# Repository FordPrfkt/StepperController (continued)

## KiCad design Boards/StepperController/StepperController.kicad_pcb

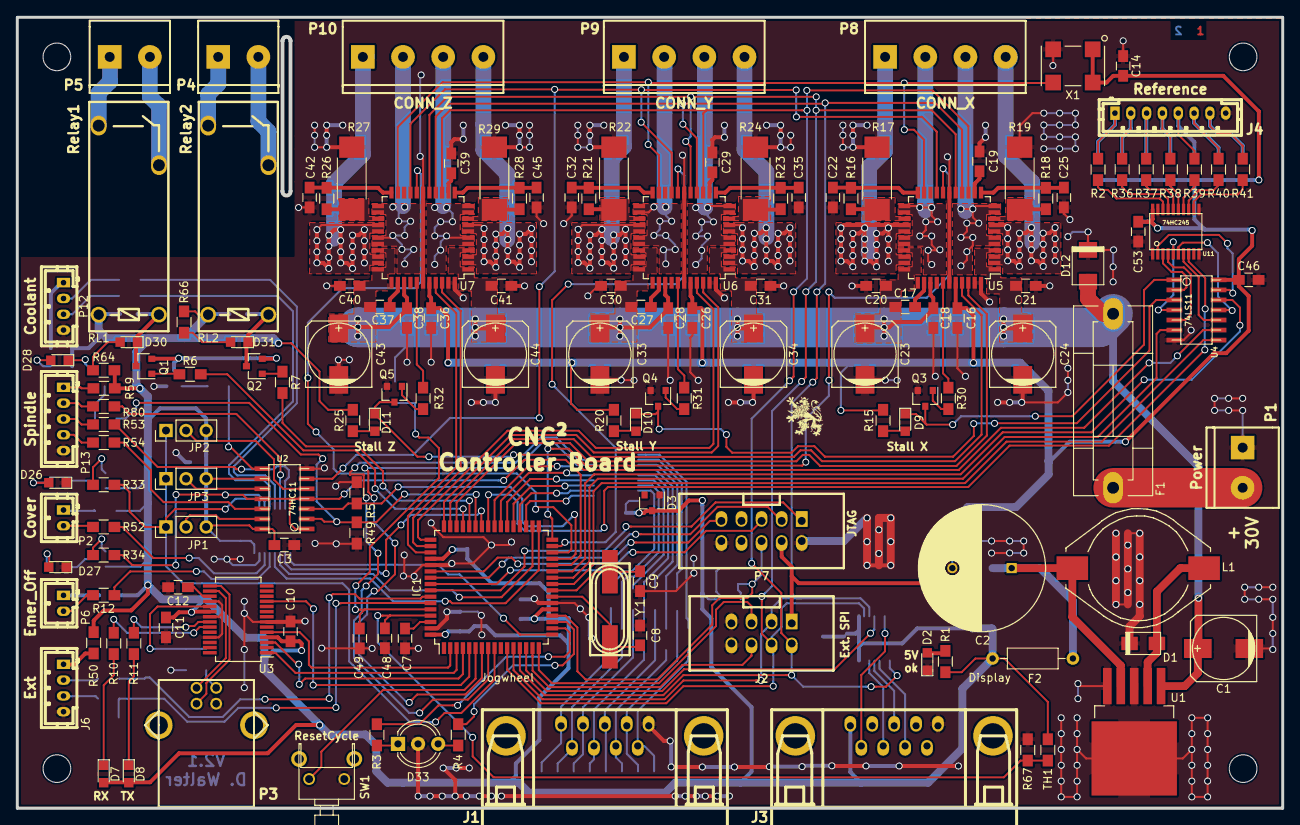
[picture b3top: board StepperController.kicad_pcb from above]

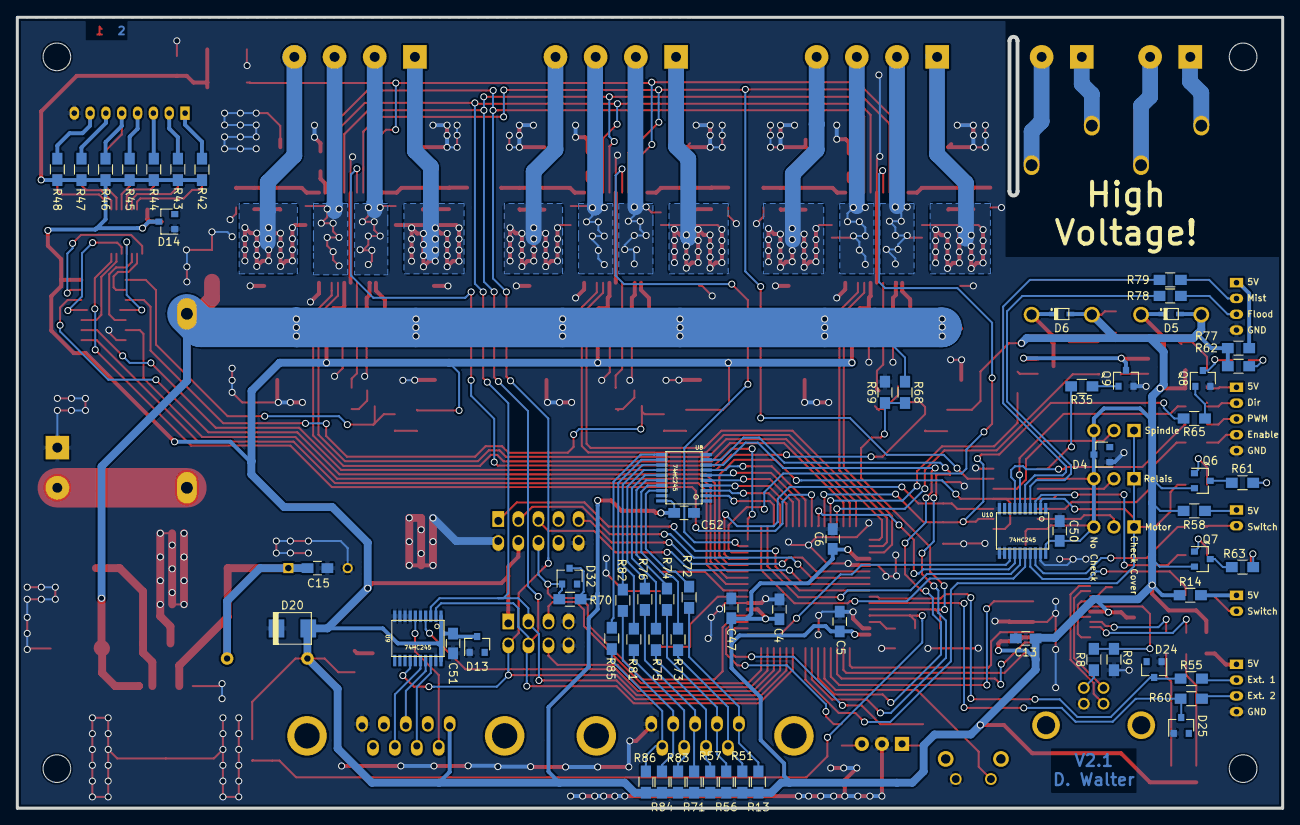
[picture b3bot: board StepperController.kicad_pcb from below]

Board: 2 copper layers, 160.0 x 100.0 mm, 213 parts (65 on the bottom side), 204 nets.

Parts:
C1, C23, C24, C33, C34, C43, C44: 100µF; c_elec_8x10.5
C2: 1000µF; C_Radial_D16_L25_P7.5
C3, C4, C5, C6, C7, C10, C12, C14, C16, C17, C18, C20, C21, C26, C27, C28, C30, C31, C36, C37, C38, C40, C41, C46, C48, C49, C50, C51, C52, C53: 100nF; C_0805_HandSoldering
C8, C9: 22pF; C_0805_HandSoldering
C11: 100nf; C_0805_HandSoldering
C13: 4,7µF; C_0805_HandSoldering
C15, C47: 10µF; C_0805_HandSoldering
C19, C29, C32, C39: 470nF; C_0805_HandSoldering
C22, C25, C35, C42, C45: 10nF; C_0805_HandSoldering
D1: SK34; do214ac
D2: LED_GN; LED_0805
D3, D4, D13, D14, D24, D25: ZMY5,6; D_SOT-23_ANK
D5, D6: 1N4148; sod323
D7, D8: LED_YE; LED_0805
D9, D10, D11: LED_RT; LED_0805
D12: SM6T 30CA; do214aa
D20: P6SMB 6,8A; do214aa
D26, D27: LED_Rd; LED_0805
D28, D30, D31: LED_Gn; LED_0805
D32: ZMY5.6; D_SOT-23_ANK
D33: Led_x2; LED_D5.0mm-3
F1: 10AT; Fuseholder5x20_horiz_SemiClosed_Casing10x25mm
F2: 4AT; R_Axial_DIN0207_L6.3mm_D2.5mm_P10.16mm_Horizontal
IC1: ATMEGA128-A; TQFP-64_14x14mm_Pitch0.8mm
J1, J3: DB9_Female; DB_9F
J2: SPI_Extern; vasch_strip_4x2
J4: Reference; b8b-ph-kl
J6: Ext; b4b-ph-kl
JP1, JP2, JP3: JUMPER3; Pin_Header_Straight_1x03_Pitch2.54mm
L1: L-PISR 100µH; Choke_SMD_PISR_Handsoldering_FASTRON
P1: Power; mors_2p
P2: Cover; b2b-ph-kl
P3: USB_B; conn_usb_B
P4: Relay2; mors_2p
P5: Relay1; mors_2p
P6: Emer_Off; b2b-ph-kl
P7: JTAG; vasch_strip_5x2
P8: CONN_X; mors_4p
P9: CONN_Y; mors_4p
P10: CONN_Z; mors_4p
P12: Coolant; b4b-ph-kl
P13: Spindle; b5b-ph-kl
Q1, Q2, Q3, Q4, Q5, Q8, Q9: BC817-40; SOT-23
Q6, Q7: BC807-40; SOT-23
R1, R3, R62, R64, R66: 140R; R_0805_HandSoldering
R2, R12, R14, R36, R37, R38, R39, R40, R41, R52, R53, R54, R55, R58, R60, R72, R73, R74, R75, R76, R78, R79, R80, R81, R82, R85: 100R; R_0805_HandSoldering
R4, R15, R20, R25, R61, R63: 160R; R_0805_HandSoldering
R5, R9, R49: 10k; R_0805_HandSoldering
R6, R7, R33, R34, R35: 1k; R_0805_HandSoldering
R8, R13, R30, R31, R32, R42, R43, R44, R45, R46, R47, R48, R51, R56, R57, R65, R71, R83, R84, R86: 4k7; R_0805_HandSoldering
R10, R11: 150R; R_0805_HandSoldering
R16, R18, R23, R26, R28: 22R; R_0805_HandSoldering
R17, R19, R24, R27, R29: 100mR; R_2512_HandSoldering
R21, R50, R59, R77: 10R; R_0805_HandSoldering
R22: 150mR; R_2512_HandSoldering
R67: 3k6; R_0805_HandSoldering
R68: 8k6; R_0805_HandSoldering
R69: 1k2; R_0805_HandSoldering
R70: 12k; R_0805_HandSoldering
RL1, RL2: FINDER-36.11-4301; Fujiutsu_JS-MT
SW1: ResetCycle; SW_0773
TH1: 6k8; R_0805_HandSoldering
U1: LM2576S-5; TO-263-5Lead
U2: 74HC11; so-14
U3: FT232RL; SSOP-28_5.3x10.2mm_Pitch0.65mm
U4: 74LS11; so-14
U5, U6, U7: TMC2660; TQFP-44_10x10mm_Pitch0.8mm
U8, U9, U10, U11: 74HC245; tssop-20
X1: 16MHz; XO91
Y1: 16MHz; hc-49_smd

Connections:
+5V: C3.1, C4.1, C5.1, C6.1, C10.1, C11.1, C13.1, C14.1, C16.1, C26.1, C36.1, C46.1, C47.1, C50.1, C51.1, C52.1, C53.1, D3.1, D4.1, D5.1, D6.1, D7.2, D8.2, D13.1, D14.1, D20.1, D32.1, F2.2, IC1.21, IC1.52, IC1.64, J2.1, J3.5, JP1.3, JP2.3, JP3.3, P7.4, Q6.2, Q7.2, R1.1, R13.1, R14.1, R15.1, R20.1, R25.2, R42.1, R43.1, R44.1, R45.1, R46.1, R47.1, R48.1, R50.1, R51.1, R56.1, R57.1, R58.1, R59.1, R62.1, R64.1, R66.1, R70.1, R71.1, R77.1, R83.1, R84.1, R86.1, RL1.A1, RL2.A1, TH1.1, U2.9, U2.14, U3.4, U3.20, U4.14, U5.40, U6.40, U7.40, U8.20, U9.1, U9.20, U10.20, U11.20, X1.1, X1.4
/Controller/CS_Ext1: IC1.15, J2.6
/Controller/CS_Ext2: IC1.16, J2.5
/Controller/CS_X: IC1.32, U5.18
/Controller/CS_Y: IC1.31, U6.18
/Controller/CS_Z: IC1.30, U7.18
/Controller/CTS: IC1.5, U3.11
/Controller/Cool_Flood: IC1.33, U10.16
/Controller/Cool_Mist: IC1.34, U10.15
/Controller/Cover: IC1.9, JP1.1, JP2.1, JP3.1, R33.2, U10.2
/Controller/CycleStart: IC1.8, U8.9
/Controller/Dir_X: IC1.47, U5.41
/Controller/Dir_Y: IC1.49, U6.41
/Controller/Dir_Z: IC1.51, U7.41
/Controller/Emergency_Off: IC1.28, R34.2, U2.1, U2.4, U2.11, U10.3
/Controller/Enable: IC1.29, R5.1, U2.3
/Controller/Ext1: D24.1, IC1.58, R55.1
/Controller/Ext2: D25.1, IC1.59, R60.1
/Controller/FeedHold: IC1.7, U8.8
/Controller/JogA: IC1.35, U8.2
/Controller/JogB: IC1.36, U8.3
/Controller/JogC: IC1.37, U8.4
/Controller/JogX: IC1.38, U8.5
/Controller/JogY: IC1.39, U8.6
/Controller/JogZ: IC1.40, U8.7
/Controller/LED1: IC1.18, R3.2
/Controller/LED2: IC1.19, R4.2
/Controller/RTS: IC1.4, U3.3
/Controller/RXD: IC1.2, U3.5
/Controller/Ref_X1: U4.13, U11.2
/Controller/Ref_X2: U4.2, U11.3
/Controller/Ref_Y1: U4.5, U11.4
/Controller/Ref_Y2: U4.4, U11.5
/Controller/Ref_Z1: U4.11, U11.6
/Controller/Ref_Z2: U4.10, U11.7
/Controller/Rel_1: IC1.45, R6.2
/Controller/Rel_2: IC1.44, R7.2
/Controller/Reset: D32.2, IC1.20, P7.6, R70.2
/Controller/SCK: IC1.11, J2.4, U5.16, U6.16, U7.16, U9.2
/Controller/SDI: IC1.12, J2.3, U5.15, U6.15, U7.15, U9.3
/Controller/SDO: IC1.13, J2.2, U5.14, U6.14, U7.14, U9.14
/Controller/Spindle_Dir: IC1.42, U10.14
/Controller/Spindle_PWM: IC1.17, U10.13
/Controller/Stall_X: D9.1, Q3.3, U4.1
/Controller/Stall_Y: D10.1, Q4.3, U4.3
/Controller/Stall_Z: D11.1, Q5.3, U4.9
/Controller/Step_X: IC1.46, U5.42
/Controller/Step_Y: IC1.48, U6.42
/Controller/Step_Z: IC1.50, U7.42
/Controller/TXD: IC1.3, U3.1
/Controller/T_REG: C48.1, IC1.61, R67.1, TH1.2
/Controller/V_SUP: C49.1, IC1.60, R68.2, R69.1
/Driver/Driver_X/BRA_X: R18.1, R19.2, U5.9
/Driver/Driver_X/BRB_X: R16.1, R17.2, U5.25
/Driver/Driver_X/OA1_X: P8.4, U5.2, U5.3, U5.7, U5.8
/Driver/Driver_X/OA2_X: P8.3, U5.5, U5.6, U5.10, U5.11
/Driver/Driver_X/OB1_X: P8.1, U5.26, U5.27, U5.31, U5.32
/Driver/Driver_X/OB2_X: P8.2, U5.23, U5.24, U5.28, U5.29
/Driver/Driver_X/SRA_X: C25.2, R18.2, U5.12
/Driver/Driver_X/SRB_X: C22.2, R16.2, U5.22
/Driver/Driver_Y/BRA_Y: R23.1, R24.2, U6.9
/Driver/Driver_Y/BRB_Y: R21.1, R22.2, U6.25
/Driver/Driver_Y/OA1_Y: P9.4, U6.2, U6.3, U6.7, U6.8
/Driver/Driver_Y/OA2_Y: P9.3, U6.5, U6.6, U6.10, U6.11
/Driver/Driver_Y/OB1_Y: P9.1, U6.26, U6.27, U6.31, U6.32
/Driver/Driver_Y/OB2_Y: P9.2, U6.23, U6.24, U6.28, U6.29
/Driver/Driver_Y/SRA_Y: C35.2, R23.2, U6.12
/Driver/Driver_Y/SRB_Y: C32.2, R21.2, U6.22
/Driver/Driver_Z/BRA_Z: R28.1, R29.2, U7.9
/Driver/Driver_Z/BRB_Z: R26.1, R27.2, U7.25
/Driver/Driver_Z/OA1_Z: P10.4, U7.2, U7.3, U7.7, U7.8
/Driver/Driver_Z/OA2_Z: P10.3, U7.5, U7.6, U7.10, U7.11
/Driver/Driver_Z/OB1_Z: P10.1, U7.26, U7.27, U7.31, U7.32
/Driver/Driver_Z/OB2_Z: P10.2, U7.23, U7.24, U7.28, U7.29
/Driver/Driver_Z/SRA_Z: C45.2, R28.2, U7.12
/Driver/Driver_Z/SRB_Z: C42.2, R26.2, U7.22
/Driver/TMC_Clock: U5.21, U6.21, U7.21, X1.3
/Driver/TMC_Enable: U2.6, U5.19, U6.19, U7.19
/Interface/CS_Disp: IC1.14, U9.4
/Interface/D+: P3.3, U3.15
/Interface/D-: P3.2, U3.16
/Interface/LED_RX: R11.2, U3.22
/Interface/LED_TX: R10.2, U3.23
/Interface/Ref_T1: IC1.41, U11.8
/Interface/Reset_UART: R8.2, R9.1, U3.19
/Interface/Spindle_Enable: IC1.43, R49.2, R65.2, U2.2
/Interface/VCC_USB: P3.1, R8.1
GND: C1.2, C2.2, C3.2, C4.2, C5.2, C6.2, C7.2, C8.2, C9.2, C10.2, C11.2, C12.2, C13.2, C14.2, C15.2, C16.2, C18.2, C19.2, C20.2, C21.2, C22.1, C23.2, C24.2, C25.1, C26.2, C28.2, C29.2, C30.2, C31.2, C32.1, C33.2, C34.2, C35.1, C36.2, C38.2, C39.2, C40.2, C41.2, C42.1, C43.2, C44.2, C45.1, C46.2, C47.2, C48.2, C49.2, C50.2, C51.2, C52.2, C53.2, D1.2, D2.1, D3.2, D4.2, D12.2, D13.2, D14.2, D20.2, D24.2, D25.2, D26.1, D27.1, D33.2, IC1.22, IC1.53, IC1.63, J1.1, J2.7, J2.8, J3.1, J4.8, J6.4, P1.1, P3.4, P7.2, P7.10, P12.4, P13.5, Q3.2, Q4.2, Q5.2, Q8.2, Q9.2, R5.2, R9.2, R17.1, R19.1, R22.1, R24.1, R27.1, R29.1, R49.1, R67.2, R69.2, SW1.2, U1.3, U1.5, U2.7, U3.7, U3.18, U3.21, U3.25, U4.7, U5.17, U5.39, U5.43, U5.44, U6.17, U6.39, U6.43, U6.44, U7.17, U7.39, U7.43, U7.44, U8.1, U8.10, U8.19, U9.5, U9.7, U9.8, U9.9, U9.10, U9.19, U10.1, U10.10, U10.11, U10.12, U10.19, U11.1, U11.10, U11.11, U11.19, X1.2
unnamed: C7.1, IC1.62
unnamed: C8.1, IC1.23, Y1.2
unnamed: C9.1, IC1.24, Y1.1
unnamed: C12.1, U3.17
unnamed: C2.1, C15.1, F2.1, L1.2, U1.4
unnamed: C17.2, U5.35
unnamed: C19.1, U5.13
unnamed: C27.2, U6.35
unnamed: C29.1, U6.13
unnamed: C37.2, U7.35
unnamed: C39.1, U7.13
unnamed: D1.1, L1.1, U1.2
unnamed: D2.2, R1.2
unnamed: D7.1, R10.1
unnamed: D8.1, R11.1
unnamed: D9.2, R15.2
unnamed: D10.2, R20.2
unnamed: D11.2, R25.1
unnamed: D26.2, R61.1
unnamed: D27.2, R63.2
unnamed: D28.1, Q8.3
unnamed: D28.2, R62.2
unnamed: D5.2, D30.1, Q1.3, RL1.A2
unnamed: D30.2, R64.2
unnamed: D6.2, D31.1, Q2.3, RL2.A2
unnamed: D31.2, R66.2
unnamed: D33.1, R3.1
unnamed: D33.3, R4.1
unnamed: F1.1, P1.2
unnamed: IC1.6, SW1.1
unnamed: IC1.25, U4.8
unnamed: IC1.26, U4.6
unnamed: IC1.27, U4.12
unnamed: IC1.54, P7.9
unnamed: IC1.55, P7.3
unnamed: IC1.56, P7.5
unnamed: IC1.57, P7.1
unnamed: J1.2, R82.2, R84.2
unnamed: J1.3, R71.2, R76.2
unnamed: J1.4, R56.2, R74.2
unnamed: J1.5, R13.2, R72.2
unnamed: J1.6, R85.2, R86.2
unnamed: J1.7, R81.2, R83.2
unnamed: J1.8, R57.2, R75.2
unnamed: J1.9, R51.2, R73.2
unnamed: J3.3, U9.17
unnamed: J3.7, U9.16
unnamed: J3.8, U9.18
unnamed: J3.9, U9.6
unnamed: J4.1, R2.2, R42.2
unnamed: J4.2, R36.2, R43.2
unnamed: J4.3, R37.2, R44.2
unnamed: J4.4, R38.2, R45.2
unnamed: J4.5, R39.2, R46.2
unnamed: J4.6, R40.2, R47.2
unnamed: J4.7, R41.2, R48.2
unnamed: J6.1, R50.2
unnamed: J6.2, R55.2
unnamed: J6.3, R60.2
unnamed: JP1.2, U2.13
unnamed: JP2.2, U2.5
unnamed: JP3.2, U2.10
unnamed: P2.1, R58.2
unnamed: P2.2, R52.2
unnamed: P4.1, RL2.14
unnamed: P4.2, RL2.11
unnamed: P5.1, RL1.14
unnamed: P5.2, RL1.11
unnamed: P6.1, R14.2
unnamed: P6.2, R12.2
unnamed: P12.1, R77.2
unnamed: P12.2, R79.2
unnamed: P12.3, R78.2
unnamed: P13.1, R59.2
unnamed: P13.2, R80.2
unnamed: P13.3, R53.2
unnamed: P13.4, R54.2
unnamed: Q1.1, R6.1
unnamed: Q1.2, Q2.2, Q9.3
unnamed: Q2.1, R7.1
unnamed: Q3.1, R30.2
unnamed: Q4.1, R31.2
unnamed: Q5.1, R32.1
unnamed: Q6.1, R33.1
unnamed: Q6.3, R61.2
unnamed: Q7.1, R34.1
unnamed: Q7.3, R63.1
unnamed: Q8.1, R65.1
unnamed: Q9.1, R35.1
unnamed: R2.1, U11.18
unnamed: R12.1, U10.17
unnamed: R30.1, U5.38
unnamed: R31.1, U6.38
unnamed: R32.2, U7.38
unnamed: R35.2, U2.8
unnamed: R36.1, U11.17
unnamed: R37.1, U11.16
unnamed: R38.1, U11.15
unnamed: R39.1, U11.14
unnamed: R40.1, U11.13
unnamed: R41.1, U11.12
unnamed: R52.1, U10.18
unnamed: R53.1, U10.7
unnamed: R54.1, U2.12
unnamed: R72.1, U8.18
unnamed: R73.1, U8.17
unnamed: R74.1, U8.16
unnamed: R75.1, U8.15
unnamed: R76.1, U8.14
unnamed: R78.1, U10.4
unnamed: R79.1, U10.5
unnamed: R80.1, U10.6
unnamed: R81.1, U8.13
unnamed: R82.1, U8.12
unnamed: R85.1, U8.11
VSA: C1.1, C17.1, C18.1, C20.1, C21.1, C23.1, C24.1, C27.1, C28.1, C30.1, C31.1, C33.1, C34.1, C37.1, C38.1, C40.1, C41.1, C43.1, C44.1, D12.1, F1.2, R68.1, U1.1, U5.1, U5.4, U5.30, U5.33, U5.36, U6.1, U6.4, U6.30, U6.33, U6.36, U7.1, U7.4, U7.30, U7.33, U7.36

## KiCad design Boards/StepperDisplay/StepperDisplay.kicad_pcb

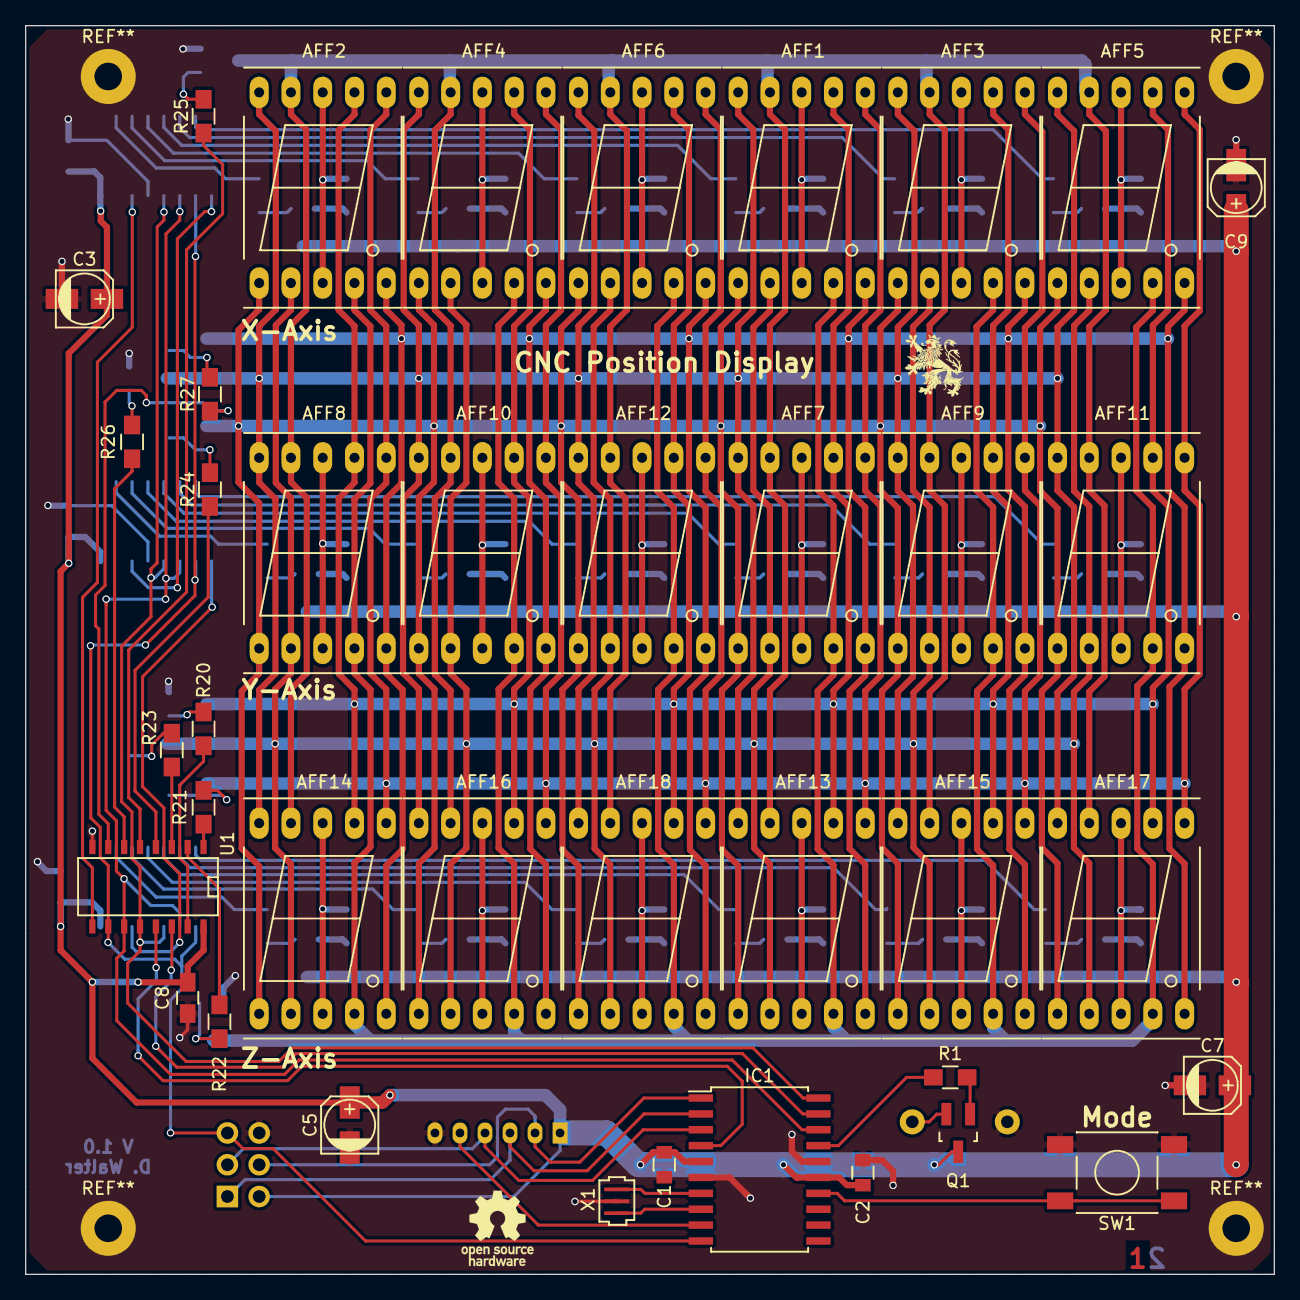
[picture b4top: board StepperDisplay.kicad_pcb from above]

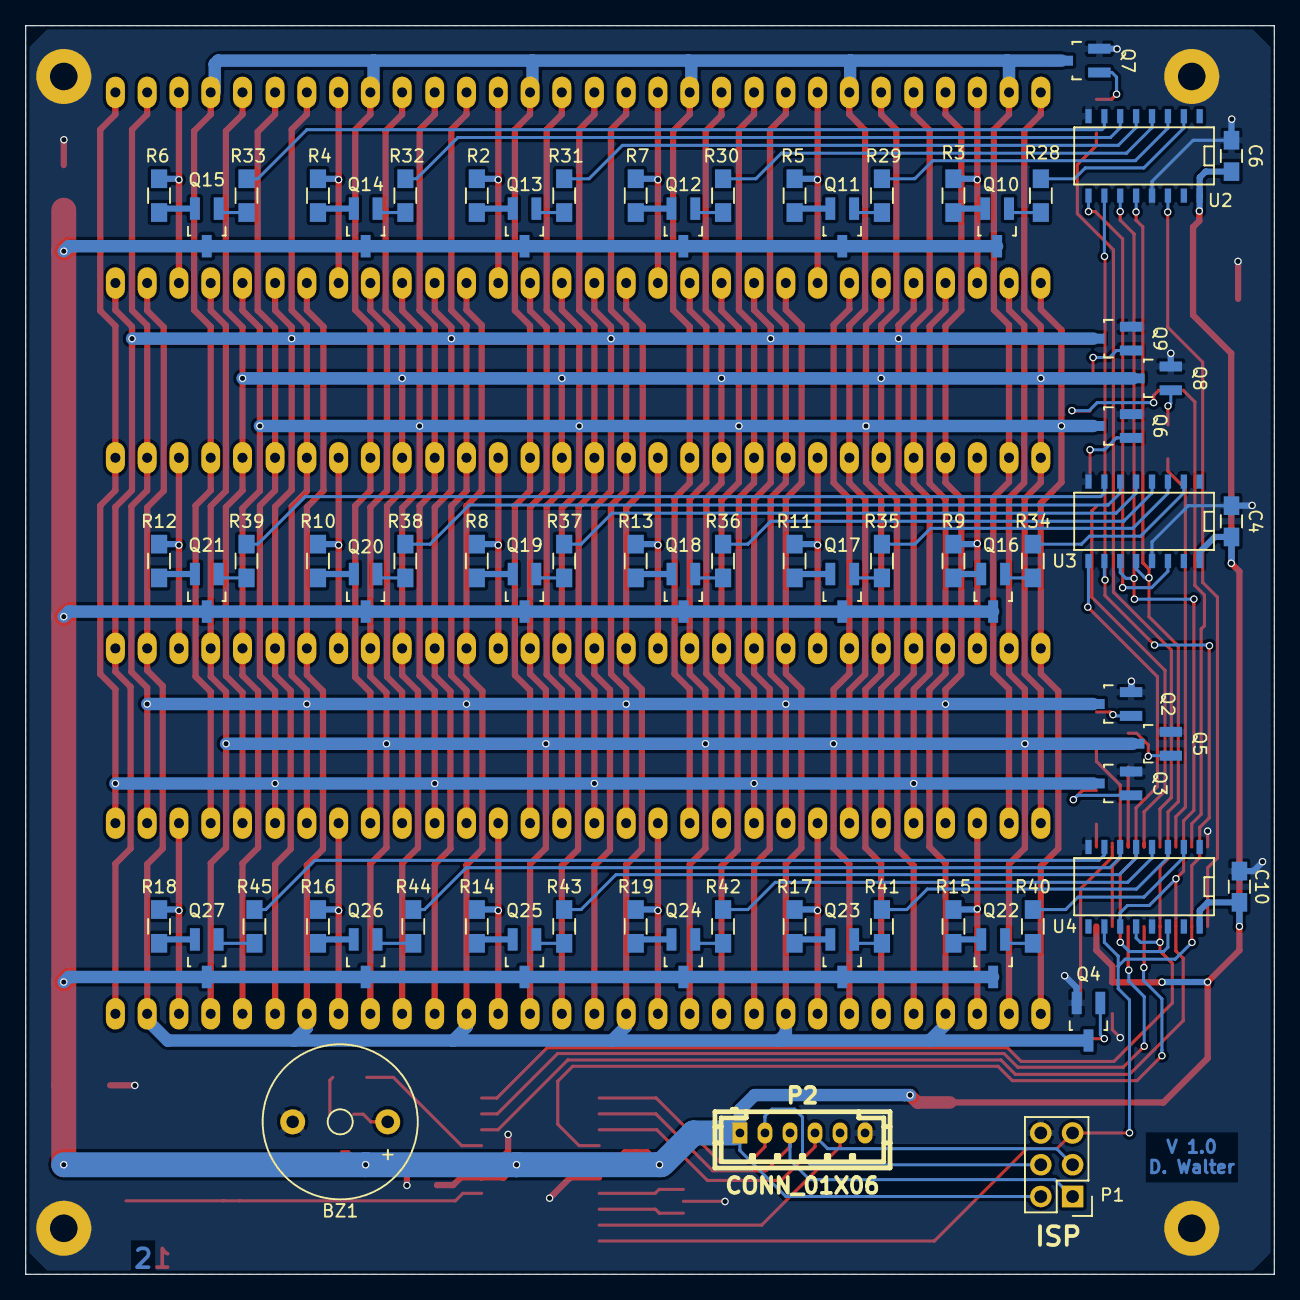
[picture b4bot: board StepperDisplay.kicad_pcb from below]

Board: 2 copper layers, 99.8 x 99.8 mm, 110 parts (71 on the bottom side), 116 nets.

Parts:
AFF1, AFF2, AFF3, AFF4, AFF5, AFF6, AFF7, AFF8, AFF9, AFF10, AFF11, AFF12, AFF13, AFF14, AFF15, AFF16, AFF17, AFF18: 7SEGMENTS; 7SegmentLED_LTS6760_LTS6780
BZ1: buzzer; Buzzer_12x9.5RM7.6
C1, C2: 100nF; C_0805
C3, C5, C7, C9: 100µF; c_elec_4x5.8
C4, C6, C8, C10: 100nF; C_0805_HandSoldering
IC1: ATTINY861-P; SOIC-20_7.5x12.8mm_Pitch1.27mm
P1: ISP; Pin_Header_Straight_2x03
P2: CONN_01X06; b6b-ph-kl
Q1, Q10, Q11, Q12, Q13, Q14, Q15, Q16, Q17, Q18, Q19, Q20, Q21, Q22, Q23, Q24, Q25, Q26, Q27: BC817-40; SOT-23_Handsoldering
Q2, Q3, Q4, Q5, Q6, Q7, Q8, Q9: IRLML2502; SOT-23_Handsoldering
R1, R28, R29, R30, R31, R32, R33, R34, R35, R36, R37, R38, R39, R40, R41, R42, R43, R44, R45: 1k; R_0805_HandSoldering
R2, R3, R4, R5, R6, R7, R8, R9, R10, R11, R12, R13, R14, R15, R16, R17, R18, R19: 18R; R_0805_HandSoldering
R20, R21, R22, R23, R24, R25, R26, R27: 100R; R_0805_HandSoldering
SW1: SW_PUSH; SW_LSx_1301
U1, U2, U3, U4: 74HC595; SO-16-N
X1: 12MHz; Resonator_CSTCE

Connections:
+5V: C1.1, C2.1, C3.1, C4.1, C5.1, C6.1, C7.1, C8.1, C9.1, C10.1, IC1.5, IC1.15, P1.2, P2.1, Q1.3, Q10.3, Q11.3, Q12.3, Q13.3, Q14.3, Q15.3, Q16.3, Q17.3, Q18.3, Q19.3, Q20.3, Q21.3, Q22.3, Q23.3, Q24.3, Q25.3, Q26.3, Q27.3, U1.16, U2.16, U3.16, U4.16
/Controller/Enable: IC1.4, U1.13
/Controller/R_Clock: IC1.20, U1.12, U2.12, U3.12, U4.12
/Controller/Reset: IC1.10, P1.5, U1.10, U2.10, U3.10, U4.10
/Controller/Ser_Clock: IC1.18, U1.11, U2.11, U3.11, U4.11
/LEDS/LEDsX/Ser_In: U1.9, U2.14
/LEDS/LEDsY/Ser_In: U2.9, U3.14
/LEDS/LEDsZ/Ser_In: U3.9, U4.14
/LEDS/Q1: R20.2, U1.15
/LEDS/Q2: R21.2, U1.1
/LEDS/Q3: R22.2, U1.2
/LEDS/Q4: R23.2, U1.3
/LEDS/Q5: R24.2, U1.4
/LEDS/Q6: R25.2, U1.5
/LEDS/Q7: R26.2, U1.6
/LEDS/Q8: R27.2, U1.7
/LEDS/Ser_In: IC1.19, U1.14
GND: BZ1.2, C1.2, C2.2, C3.2, C4.2, C5.2, C6.2, C7.2, C8.2, C9.2, C10.2, IC1.6, IC1.16, P1.6, P2.6, Q2.2, Q3.2, Q4.2, Q5.2, Q6.2, Q7.2, Q8.2, Q9.2, SW1.2, U1.8, U2.8, U2.13, U3.8, U3.13, U4.8, U4.13, X1.2
unnamed: AFF1.3, AFF1.8, R2.2
unnamed: AFF2.3, AFF2.8, R3.2
unnamed: AFF3.3, AFF3.8, R4.2
unnamed: AFF4.3, AFF4.8, R5.2
unnamed: AFF5.3, AFF5.8, R6.2
unnamed: AFF6.3, AFF6.8, R7.2
unnamed: AFF7.3, AFF7.8, R8.2
unnamed: AFF8.3, AFF8.8, R9.2
unnamed: AFF9.3, AFF9.8, R10.2
unnamed: AFF10.3, AFF10.8, R11.2
unnamed: AFF11.3, AFF11.8, R12.2
unnamed: AFF12.3, AFF12.8, R13.2
unnamed: AFF13.3, AFF13.8, R14.2
unnamed: AFF14.3, AFF14.8, R15.2
unnamed: AFF15.3, AFF15.8, R16.2
unnamed: AFF16.3, AFF16.8, R17.2
unnamed: AFF17.3, AFF17.8, R18.2
unnamed: AFF18.3, AFF18.8, R19.2
unnamed: BZ1.1, Q1.2
unnamed: IC1.1, P1.4, P2.2
unnamed: IC1.2, P1.1, P2.3
unnamed: IC1.3, P1.3, P2.4
unnamed: IC1.7, X1.3
unnamed: IC1.8, X1.1
unnamed: IC1.9, P2.5
unnamed: IC1.14, SW1.1
unnamed: IC1.17, R1.2
unnamed: Q1.1, R1.1
unnamed: Q2.1, R20.1
unnamed: Q3.1, R21.1
unnamed: Q4.1, R22.1
unnamed: Q5.1, R23.1
unnamed: Q6.1, R24.1
unnamed: Q7.1, R25.1
unnamed: Q8.1, R26.1
unnamed: Q9.1, R27.1
unnamed: Q10.1, R28.1
unnamed: Q10.2, R3.1
unnamed: Q11.1, R29.1
unnamed: Q11.2, R5.1
unnamed: Q12.1, R30.1
unnamed: Q12.2, R7.1
unnamed: Q13.1, R31.1
unnamed: Q13.2, R2.1
unnamed: Q14.1, R32.1
unnamed: Q14.2, R4.1
unnamed: Q15.1, R33.1
unnamed: Q15.2, R6.1
unnamed: Q16.1, R34.1
unnamed: Q16.2, R9.1
unnamed: Q17.1, R35.1
unnamed: Q17.2, R11.1
unnamed: Q18.1, R36.1
unnamed: Q18.2, R13.1
unnamed: Q19.1, R37.1
unnamed: Q19.2, R8.1
unnamed: Q20.1, R38.1
unnamed: Q20.2, R10.1
unnamed: Q21.1, R39.1
unnamed: Q21.2, R12.1
unnamed: Q22.1, R40.1
unnamed: Q22.2, R15.1
unnamed: Q23.1, R41.1
unnamed: Q23.2, R17.1
unnamed: Q24.1, R42.1
unnamed: Q24.2, R19.1
unnamed: Q25.1, R43.1
unnamed: Q25.2, R14.1
unnamed: Q26.1, R44.1
unnamed: Q26.2, R16.1
unnamed: Q27.1, R45.1
unnamed: Q27.2, R18.1
unnamed: R28.2, U2.2
unnamed: R29.2, U2.3
unnamed: R30.2, U2.4
unnamed: R31.2, U2.5
unnamed: R32.2, U2.6
unnamed: R33.2, U2.7
unnamed: R34.2, U3.2
unnamed: R35.2, U3.3
unnamed: R36.2, U3.4
unnamed: R37.2, U3.5
unnamed: R38.2, U3.6
unnamed: R39.2, U3.7
unnamed: R40.2, U4.2
unnamed: R41.2, U4.3
unnamed: R42.2, U4.4
unnamed: R43.2, U4.5
unnamed: R44.2, U4.6
unnamed: R45.2, U4.7
Seg1: AFF1.7, AFF2.7, AFF3.7, AFF4.7, AFF5.7, AFF6.7, AFF7.7, AFF8.7, AFF9.7, AFF10.7, AFF11.7, AFF12.7, AFF13.7, AFF14.7, AFF15.7, AFF16.7, AFF17.7, AFF18.7, Q2.3
Seg2: AFF1.6, AFF2.6, AFF3.6, AFF4.6, AFF5.6, AFF6.6, AFF7.6, AFF8.6, AFF9.6, AFF10.6, AFF11.6, AFF12.6, AFF13.6, AFF14.6, AFF15.6, AFF16.6, AFF17.6, AFF18.6, Q3.3
Seg3: AFF1.4, AFF2.4, AFF3.4, AFF4.4, AFF5.4, AFF6.4, AFF7.4, AFF8.4, AFF9.4, AFF10.4, AFF11.4, AFF12.4, AFF13.4, AFF14.4, AFF15.4, AFF16.4, AFF17.4, AFF18.4, Q4.3
Seg4: AFF1.2, AFF2.2, AFF3.2, AFF4.2, AFF5.2, AFF6.2, AFF7.2, AFF8.2, AFF9.2, AFF10.2, AFF11.2, AFF12.2, AFF13.2, AFF14.2, AFF15.2, AFF16.2, AFF17.2, AFF18.2, Q5.3
Seg5: AFF1.1, AFF2.1, AFF3.1, AFF4.1, AFF5.1, AFF6.1, AFF7.1, AFF8.1, AFF9.1, AFF10.1, AFF11.1, AFF12.1, AFF13.1, AFF14.1, AFF15.1, AFF16.1, AFF17.1, AFF18.1, Q6.3
Seg6: AFF1.9, AFF2.9, AFF3.9, AFF4.9, AFF5.9, AFF6.9, AFF7.9, AFF8.9, AFF9.9, AFF10.9, AFF11.9, AFF12.9, AFF13.9, AFF14.9, AFF15.9, AFF16.9, AFF17.9, AFF18.9, Q7.3
Seg7: AFF1.10, AFF2.10, AFF3.10, AFF4.10, AFF5.10, AFF6.10, AFF7.10, AFF8.10, AFF9.10, AFF10.10, AFF11.10, AFF12.10, AFF13.10, AFF14.10, AFF15.10, AFF16.10, AFF17.10, AFF18.10, Q8.3
Seg8: AFF1.5, AFF2.5, AFF3.5, AFF4.5, AFF5.5, AFF6.5, AFF7.5, AFF8.5, AFF9.5, AFF10.5, AFF11.5, AFF12.5, AFF13.5, AFF14.5, AFF15.5, AFF16.5, AFF17.5, AFF18.5, Q9.3

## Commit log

2016-02-11 Work in Progress
2016-02-27 Recover from damaged repository
2016-02-27 Layout Displayplatine fertig
2016-02-28 Cover-Anschluss hinzu, Schutzdioden geändert
2016-03-01 Layouting...
2016-03-03 Layouting... Neuer Oszillator für TMC
2016-03-15 Minor layout changes
2016-05-02 Fixed Part Libraries
2016-05-05 Thermal vias, changed footprint of logic ics
2016-08-24 Changed to segment multiplexing, new layout
2016-08-27 Layout Release 1
2016-09-03 Added Ext. Connector, new Layout of Supply to TMC2660
2016-09-05 Layout updated
2016-09-18 New LED Driving Scheme
2016-09-19 Pre-Release Layout
2016-09-19 Added Schematic PDF
2016-10-01 Begin implementation of Display Software
2016-10-15 Version 0.0.1
2016-10-24 Software WIP
2016-12-20 Display working
2016-12-20 Button readout working. Version 1.0 Finished
2016-12-20 Layout optimizations
2017-03-12 Added Reset Logic, Layout changes
2017-03-13 Removed Accidental commit, changed µC to ATMega128A
2017-05-08 Added Connector for Buttons & Emergency Off for Relays
2017-05-17 Final Version for Manufacturing
2017-08-27 Added Buffering for Inputs
2017-09-27 Added Buffers for I/O, Changed Pinout to be compatible with grbl
2017-09-29 Changed Footprints
2018-02-11 Removed SW, Added HandController, Small PCB changes
2019-04-07 Changed to KiCad 5.1 and added HP Stepper Driver
2019-04-07 Changed to KiCad 5.1
2019-04-07 Selected FETs
2019-07-30 Updated Layout
2019-08-04 Update HPDriver.kicad_pcb
    Layout update
2019-08-21 Changed Connector to Phoenix Type
2019-09-29 Release 1.0
2019-12-19 Changed position of LEDs, improved routing
2020-07-22 Layout v1.0 finished
2021-05-21 Added Control Logic for Enable/Step/Dir Signals
2021-11-07 Added Logic to allow local control of stepper trough µC
2021-12-10 Changed Controller to ATtiny406
2022-03-21 Moved to Kicad 6.0
2022-03-21 Minor Layout fix
2022-08-06 Changed Controller to ATmega328PB
    The ATtiny did not have enough flash
2022-08-09 Revert "Delete boards/HighPowerDriver - Kopie directory"
    This reverts commit 429dd5f8732def63523e52ec431af87c5fce2a12.
